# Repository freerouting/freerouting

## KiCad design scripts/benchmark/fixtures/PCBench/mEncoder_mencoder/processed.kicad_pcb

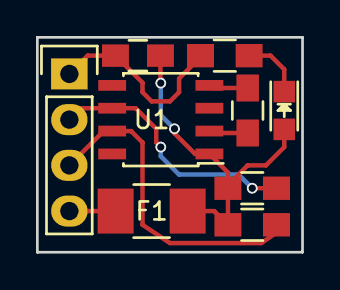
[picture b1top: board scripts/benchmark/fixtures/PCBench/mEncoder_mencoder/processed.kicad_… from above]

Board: 2 copper layers, 14.7 x 11.9 mm, 9 parts (0 on the bottom side), 8 nets.

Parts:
3V3C1: C; C_0805_HandSoldering
D3: LED:POWER; LED_0805
F1: FP_Small; C_1210_HandSoldering
P1: CONN_01X04; Pin_Header_Straight_1x04
POWERC1: C; C_0805_HandSoldering
R5: PWR; R_0805_HandSoldering
SCLUP1: R; R_0805_HandSoldering
SDAUP1: R; R_0805_HandSoldering
U1: AS5601; SOIC-8_3.9x4.9mm_Pitch1.27mm

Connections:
+5V: F1.2, P1.4
GND: P1.1, POWERC1.2, R5.2
unnamed: 3V3C1.1, U1.4
unnamed: 3V3C1.2, U1.2
unnamed: D3.1, R5.1
unnamed: P1.2, SDAUP1.2, U1.6
unnamed: P1.3, SCLUP1.2, U1.7
VCC: D3.2, F1.1, POWERC1.1, SCLUP1.1, SDAUP1.1, U1.1

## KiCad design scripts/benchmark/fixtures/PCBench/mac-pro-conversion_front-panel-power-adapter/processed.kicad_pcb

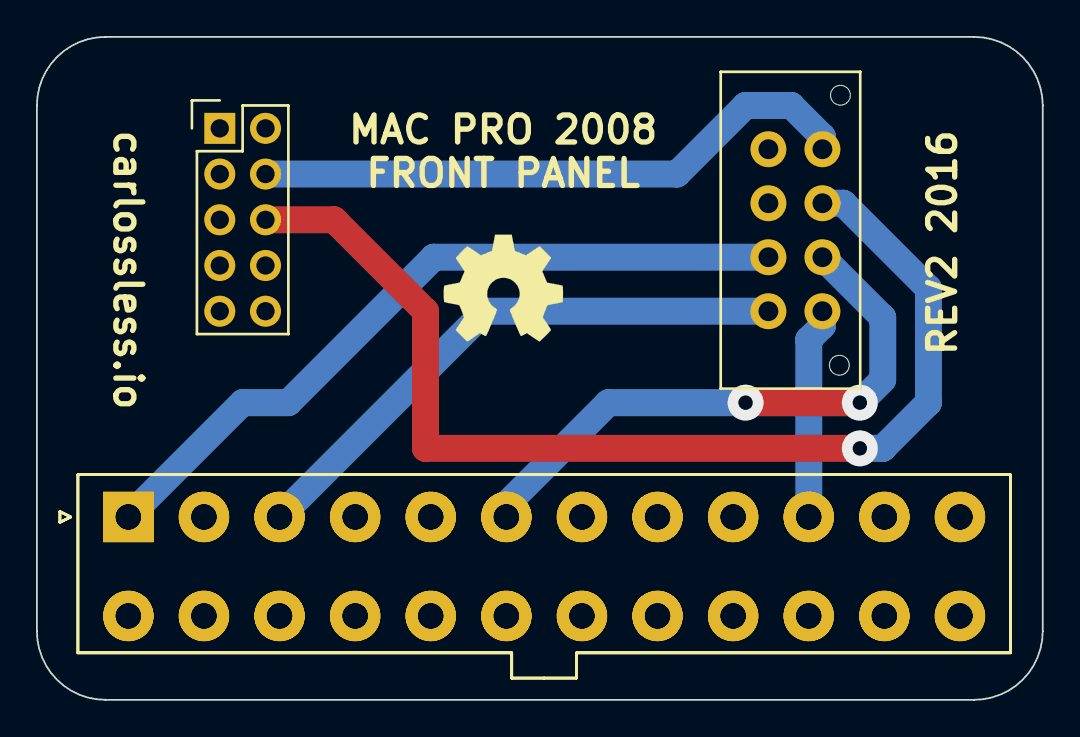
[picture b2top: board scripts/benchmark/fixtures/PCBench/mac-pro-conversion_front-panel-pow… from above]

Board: 2 copper layers, 55.9 x 36.8 mm, 4 parts (0 on the bottom side), 26 nets.

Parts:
P3: CONN_02X04; Molex_Microfit3_Header_02x04_Straight_43045-0828
P4: CONN_02X05; Pin_Header_Straight_2x05
P7, P8: CONN_02X12; Molex_MiniFit-JR-5556-24A_2x12x4.20mm_Straight

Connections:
ATX01_3.3V: P3.2, P7.1, P8.1
ATX02: P7.2, P8.2
ATX04: P7.4, P8.4
ATX06_5V: P3.6, P7.6, P8.6
ATX08: P7.8, P8.8
ATX10_12V: P3.5, P7.10, P8.10
ATX12: P7.12, P8.12
ATX14: P7.14, P8.14
ATX16: P7.16, P8.16
ATX18: P7.18, P8.18
ATX20: P7.20, P8.20
ATX22: P7.22, P8.22
ATX24: P7.24, P8.24
ATX_05: P7.5, P8.5
ATX_07: P7.7, P8.7
ATX_09: P7.9, P8.9
ATX_11: P7.11, P8.11
ATX_13: P7.13, P8.13
ATX_15: P7.15, P8.15
ATX_17: P7.17, P8.17
ATX_19: P7.19, P8.19
ATX_21: P7.21, P8.21
ATX_23: P7.23, P8.23
GND: P3.1, P7.3, P8.3
MB_MSG-: P3.8, P4.4
MB_PW+: P3.7, P4.6
